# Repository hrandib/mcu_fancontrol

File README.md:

# Intent
The main intent of this solution is to provide the functionality similar to [PC Fancontrol](https://github.com/hrandib/pc_fancontrol) service but in hardware. There are a lot of equipment around which have fans and are quite noisy for no particular reason. Some of them even have fan controllers but algo/control curve is usually awful. This module can solve this issue.

# Brief features
 - The module provides 2 fan control PWM channels.
 - The first channel optionally is able to control 2-3pin fans by regulating DC voltage
 - The second channel is PWM only, this is PCB only limitation (4-pin fans)
 - Channels have independent configuration but can use shared sensors
 - Up to 8 sensors are supported, 4 sensors of type LM75 and 4 sensors of type DS18B20
 - Each controller channel can use up to 4 sensors of any type
 - Controller define:
   - poll period
   - algorithm: PI, 2-Point
   - sensors binding
   - MIN and MAX limits for PWM
   - EMA filtering, etc
 - The module configuration is performed via UART using PC side Python utility, it uses YAML format for the store/upload

# The Basic Workflow
1. Connect all the sensors to the board
2. Connect the board to PC and set active channels, e.g if you won't use the first channel it can be disabled. The command expects the list of active channel numbers separated by space

```shell
python .\fanutil.py -p tty... -e 0 1
```
3. Optionally mark channels as analog, it's needed only for proper display in configuration file, functionality is not affected. The command expects the list of analog channel numbers separated by space, an empty means all channels are PWM 

```shell
python .\fanutil.py -p tty... -a 0
```

4. Read current configuration, it'll contain all recognized sensors and controllers template.</br>The sample config is available [here](./datasheet/sample.yaml)

```shell
python .\fanutil.py -p tty... -r fanconfig.yaml
```

5. Edit the configuration file according to the fields description
6. Upload it to the board

```shell
python .\fanutil.py -p tty... -w fanconfig.yaml
```

# Possible alternatives

China market already provides various standalone fan control modules for less than 3 bucks.<br/>In many cases it's enough to solve the issue, but there are cases that can't be covered:
 - Multiple temperature measure points required
 - Multiple controller channels required with ability to share sensors
 - Other than 2-Point algo required, e.g to stabilize the temperature on the certain level

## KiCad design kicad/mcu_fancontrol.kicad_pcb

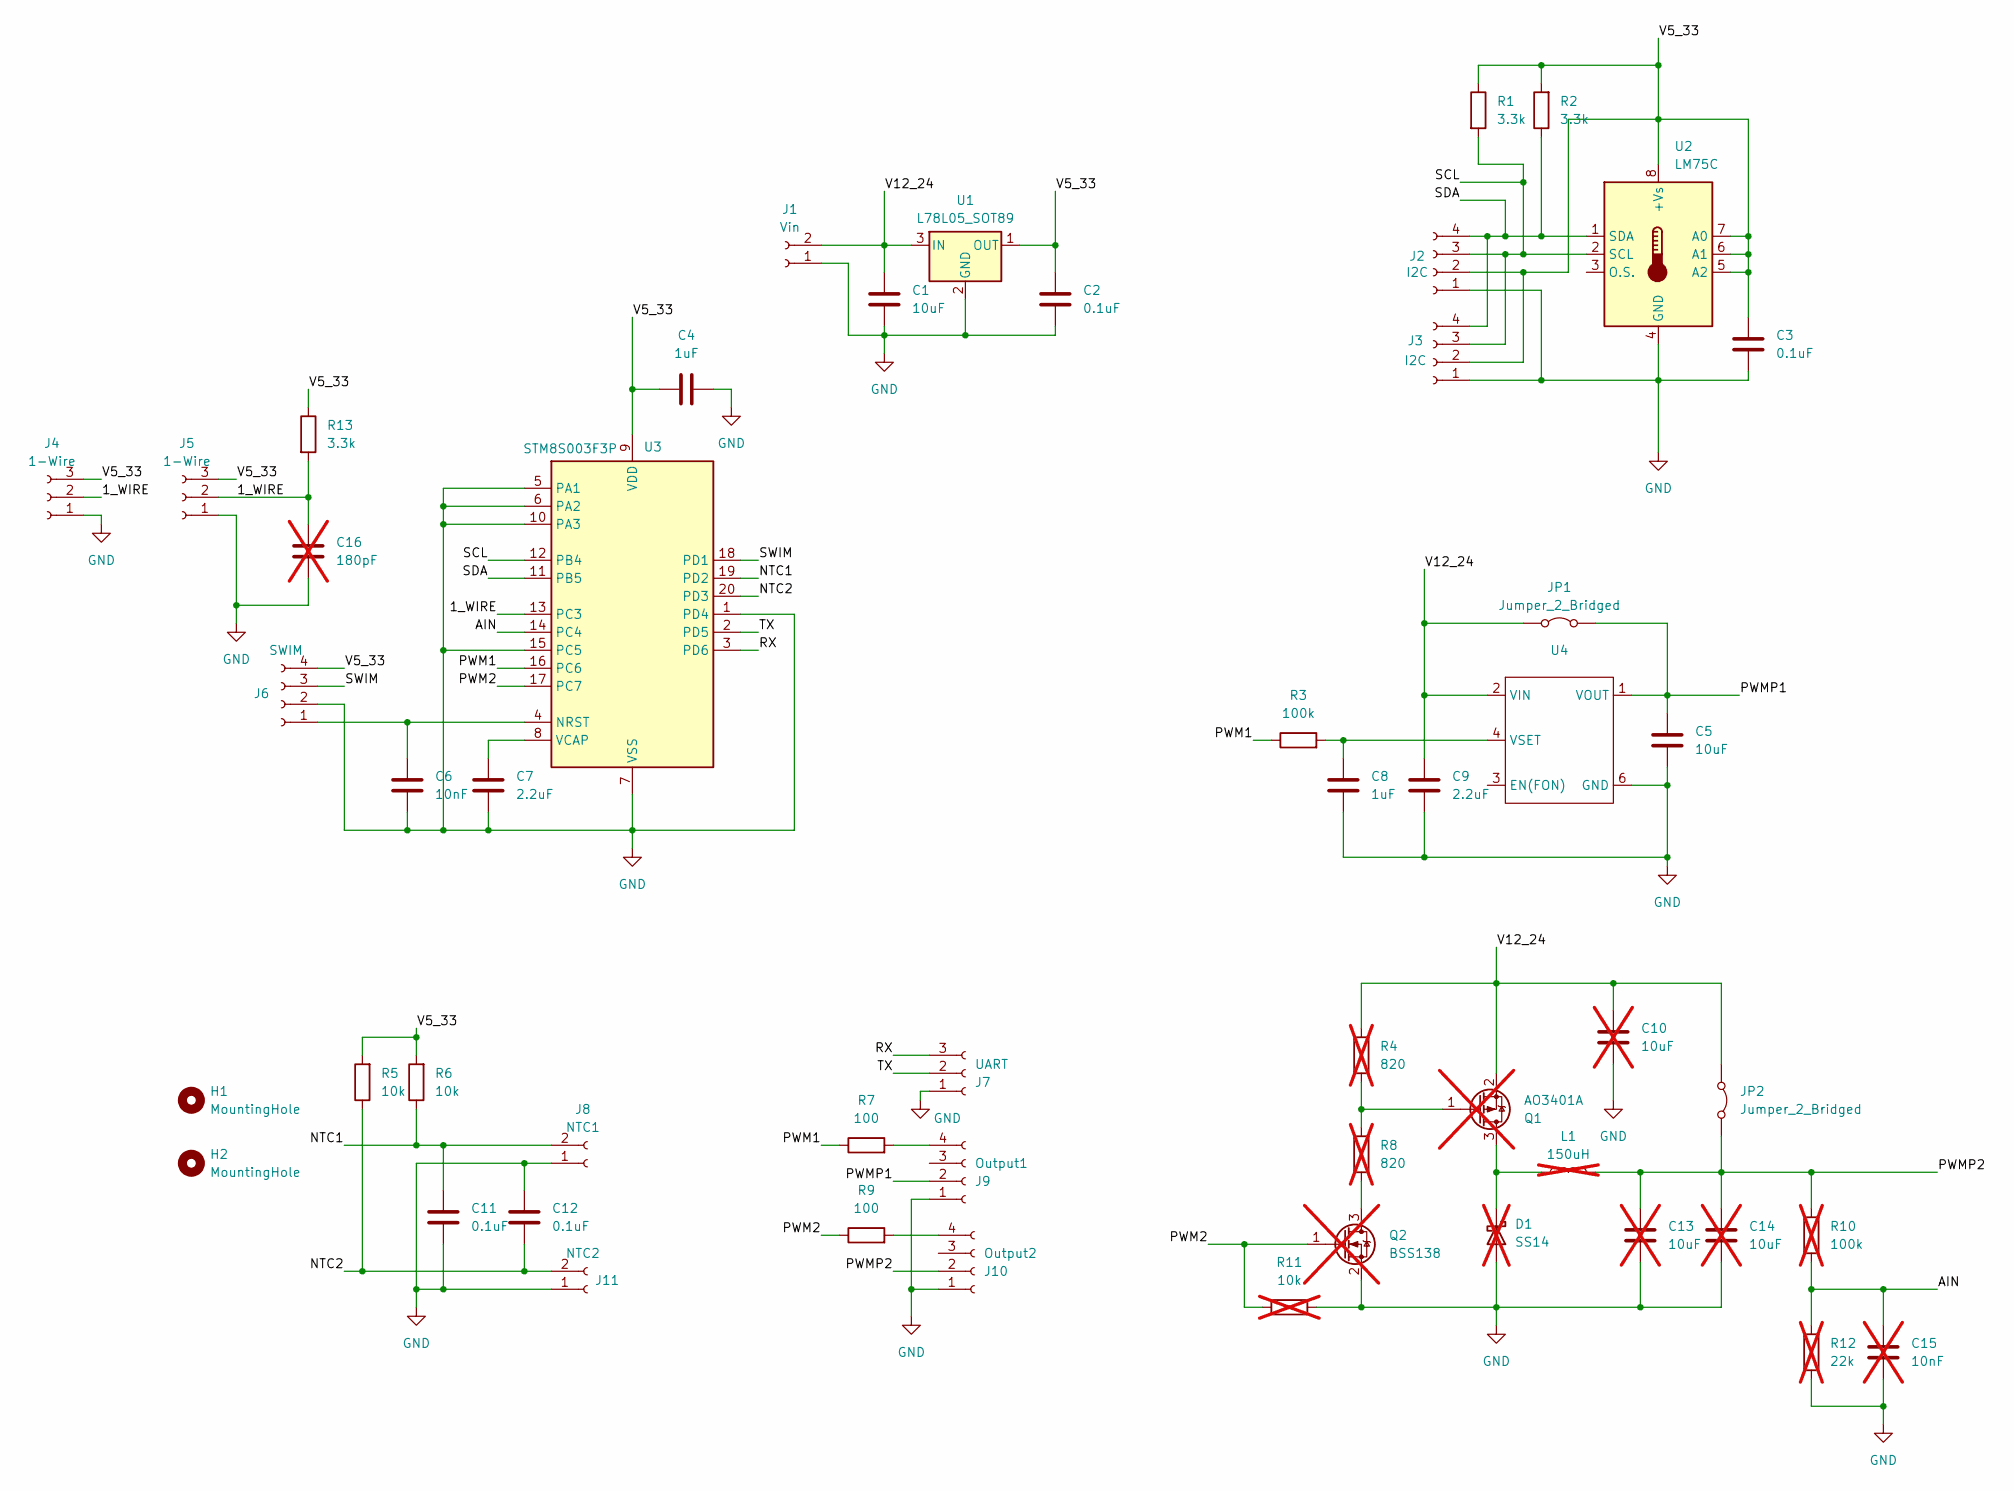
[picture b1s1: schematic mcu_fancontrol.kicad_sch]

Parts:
C1, C5: 10uF; C_1206_3216Metric
C2, C3, C11, C12: 0.1uF; C_0603_1608Metric
C4, C8: 1uF; C_0603_1608Metric
C6: 10nF; C_0603_1608Metric
C7, C9: 2.2uF; C_0603_1608Metric
C10, C13, C14: 10uF; C_1206_3216Metric; not fitted
C15: 10nF; C_0603_1608Metric; not fitted
C16: 180pF; C_0402_1005Metric_Pad0.74x0.62mm_HandSolder; not fitted
D1: SS14; D_SMA; not fitted
H1, H2: MountingHole; MountingHole_2.7mm_M2.5
J1: Vin; SolderWire-0.5sqmm_1x02_P4.8mm_D0.9mm_OD2.3mm
J2, J3: I2C; PinSocket_1x04_P2.54mm_Vertical
J4, J5: 1-Wire; PinSocket_1x03_P2.54mm_Vertical
J6: SWIM; PinSocket_1x04_P2.54mm_Vertical
J7: UART; PinSocket_1x03_P2.54mm_Vertical
J8: NTC1; PinHeader_1x02_P2.54mm_Vertical
J9: Output1; FanPinHeader_1x04_P2.54mm_Vertical
J10: Output2; FanPinHeader_1x04_P2.54mm_Vertical
J11: NTC2; PinHeader_1x02_P2.54mm_Vertical
JP1, JP2: Jumper_2_Bridged; SolderJumper-2_P1.3mm_Open_RoundedPad1.0x1.5mm
L1: 150uH; L_Radial_D7.0mm_P3.00mm; not fitted
Q1: AO3401A; SOT-23; not fitted
Q2: BSS138; SOT-23; not fitted
R1, R2, R13: 3.3k; R_0603_1608Metric
R3: 100k; R_0603_1608Metric
R4, R8: 820; R_1206_3216Metric; not fitted
R5, R6: 10k; R_0603_1608Metric
R7, R9: 100; R_0603_1608Metric
R10: 100k; R_0603_1608Metric; not fitted
R11: 10k; R_0603_1608Metric; not fitted
R12: 22k; R_0603_1608Metric; not fitted
U1: L78L05_SOT89; SOT-89-3
U2: LM75C; SOIC-8_3.9x4.9mm_P1.27mm
U3: STM8S003F3P; TSSOP-20_4.4x6.5mm_P0.65mm
U4: SOIC-8-1EP_3.9x4.9mm_P1.27mm_EP2.41x3.3mm_ThermalVias

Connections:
/1_WIRE: C16.1, J4.2, J5.2, R13.2, U3.13 (PC3)
/AIN: C15.1, R10.1, R12.2, U3.14 (PC4)
/NTC1: C11.1, J8.2, R6.1, U3.19 (PD2)
/NTC2: C12.2, J11.2, R5.1, U3.20 (PD3)
/PWM1: R3.1, R7.1, U3.16 (PC6)
/PWM2: Q2.1 (G), R9.1, R11.2, U3.17 (PC7)
/PWMP1: C5.1, J9.2, JP1.2 (B), U4.1 (VOUT)
/PWMP2: C13.2, C14.2, J10.2, JP2.2 (B), L1.2, R10.2
/RX: J7.3, U3.3 (PD6)
/SCL: J2.3, J3.3, R1.2, U2.2 (SCL), U3.12 (PB4)
/SDA: J2.4, J3.4, R2.1, U2.1 (SDA), U3.11 (PB5)
/SWIM: J6.3, U3.18 (PD1)
/TX: J7.2, U3.2 (PD5)
/V5_33: C2.1, C3.1, C4.1, J2.2, J3.2, J4.3, J5.3, J6.4, R1.1, R2.2, R5.2, R6.2, R13.1, U1.1 (OUT), U2.5 (A2), U2.6 (A1), U2.7 (A0), U2.8 (+Vs), U3.9 (VDD)
/V12_24: C1.1, C9.2, C10.2, J1.2, JP1.1 (A), JP2.1 (A), Q1.2 (S), R4.2, U1.3 (IN), U4.2 (VIN)
GND: C1.2, C2.2, C3.2, C4.2, C5.2, C6.2, C7.1, C8.1, C9.1, C10.1, C11.2, C12.1, C13.1, C14.1, C15.2, C16.2, D1.2 (A), J1.1, J2.1, J3.1, J4.1, J5.1, J6.2, J7.1, J8.1, J9.1, J10.1, J11.1, Q2.2 (S), R11.1, R12.1, U1.2 (GND), U2.4 (GND), U3.1 (PD4), U3.5 (PA1), U3.6 (PA2), U3.7 (VSS), U3.10 (PA3), U3.15 (PC5), U4.5 (NC), U4.6 (GND), U4.7 (NC), U4.8 (NC), U4.9 (PAD)
unnamed: D1.1 (K), L1.1, Q1.3 (D)
unnamed: C6.1, J6.1, U3.4 (NRST)
unnamed: J9.4, R7.2
unnamed: J10.4, R9.2
unnamed: Q1.1 (G), R4.1, R8.2
unnamed: Q2.3 (D), R8.1
unnamed: C7.2, U3.8 (VCAP)
unnamed: C8.2, R3.2, U4.4 (VSET)

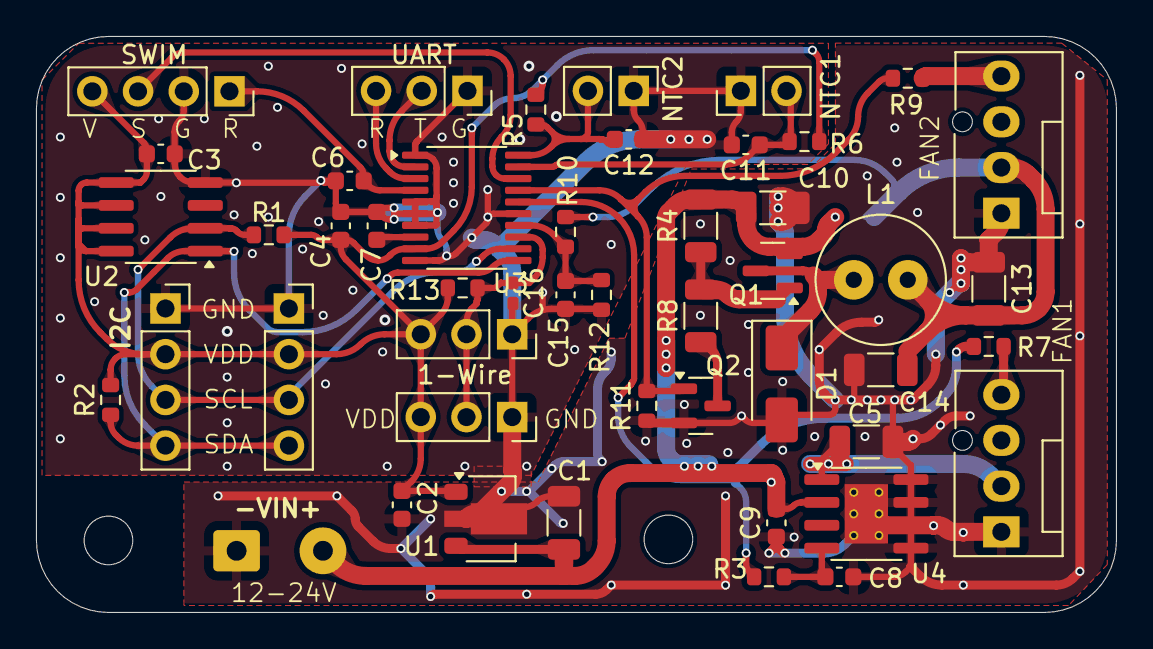
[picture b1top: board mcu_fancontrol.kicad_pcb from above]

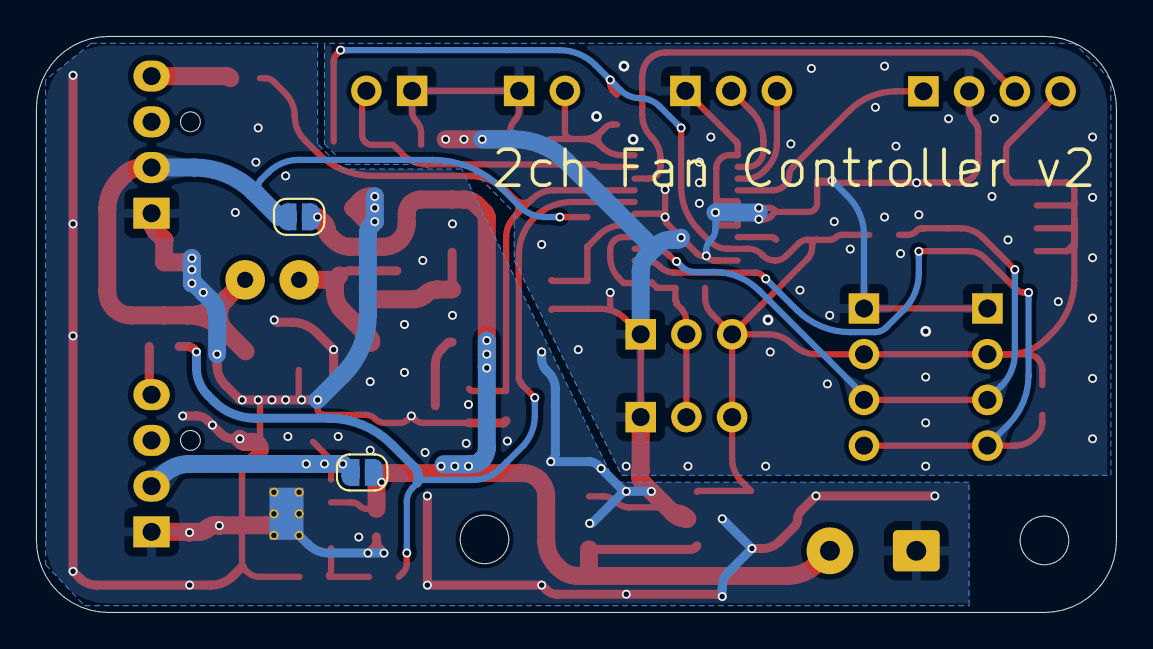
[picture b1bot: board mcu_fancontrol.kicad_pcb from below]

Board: 2 copper layers, 60.0 x 32.0 mm, 52 parts (2 on the bottom side), 24 nets.

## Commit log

2020-07-25 Initial schematic
2020-07-26 Add fan PWM specs
2020-07-26 Add pcb
2020-08-08 Add PCB connector labeling, minor design changes
2020-08-08 Add scmrtos, stm8_libs submodules
2020-08-08 Change scmrtos repo URL to own fork
2020-08-11 add qbs.user and build dir to gitignore
2020-08-11 Add base project definitions to qbs
2020-08-11 Add mcu flash script
2020-08-11 Add scmrtos and stm8lib to project build
2020-08-12 Compilation success
2020-08-15 Fully working project template
2020-08-15 LM75 driver in working state
2020-08-16 Add PWM fan control demo
2021-08-01 Fix .gitmodules syntax
2021-08-02 Fix flashing procedure
2021-08-09 Fix ScmRTOS warnings
2021-08-09 Add macros for RTOS task creation
2021-08-09 Add systicks to ms converters
2021-08-09 Cleanup main.cpp
2021-08-09 Draft implementation
2021-08-13 Add .clang-format file
2021-08-13 Reformat scmRTOS_CONFIG.h
2021-08-13 Fix MS2ST ST2MS macros
2021-08-13 Add __STDC_LIMIT_MACROS compilation option
2021-08-16 PWM Controller in the working state
2021-08-24 Move scm_utils from config to scm_aux dir
2022-02-07 Add BaseStream interface
2022-02-07 Add printing of section size
2022-02-08 Shell in the working state
2022-02-08 Remove Increment/Decrement handlers
2022-02-08 Add generic sensor interface
2022-02-08 Add DS18B20 datasheet
2022-02-08 Add missing license headers
2022-02-09 SensorHandler: add LM75 support
2022-02-09 DS18B20 reading demo
2022-02-09 Demo: print values from all sensors
2022-02-09 Tweak temperatures printing
2022-02-09 Add sample config file
2022-02-09 Remove sensor.h iface
2022-02-10 Initial controller skeleton
2022-02-10 Refactor. Drop UartStream dependency from SensorHandler
2022-02-10 Fix system timer frequency
2022-02-10 Fix sensors number handling
2022-02-10 Fix S2ST macro
2022-02-10 Rename stream arg in SHELL_FUNC
2022-02-10 Add ability to upload EEPROM content
2022-02-10 Add default EEPROM config
2022-02-11 Move PWM part to the separate module
2022-02-11 2 point algo in the working state
2022-02-11 PI algo in the working state
2022-02-11 Disable the shell due to flash size limit
2022-02-11 Fix formatting
2022-02-11 Remove shell impl
2022-02-13 Main instruction set in the working state
2022-02-14 Add support of the fan stop hysteresis
2022-02-14 Add Fan stop state GPIO output for CH2
2022-02-14 Sync stm8libs
2022-02-14 Rename Samples -> Utility
2022-02-14 Rename fancontrol.yaml -> sample.yaml
2022-02-14 Change to fixed packet size for Device info
2022-02-14 CLI utility initial implementation
2022-02-14 Add printing sensors and control structs
2022-02-15 Add crc check function
2022-02-15 Fix CRC value in the default ControlStruct
2022-02-15 Add CRC check while reading control structs
2022-02-15 Move sample configuration to Datasheet/
2022-02-15 Add ref.yaml, template config
2022-02-15 Update sample config
2022-02-15 Add config file generation
2022-02-15 Update sample remarks
2022-02-15 Add values normalization
2022-03-27 Update stm8_libs submodule
2022-05-28 Upload implemented
2022-06-12 Fix compilation on QtCreator 7
2022-06-12 Fix flashing script for QtCreator 7
2022-08-09 Make fanutil.py compatible with newer Python
2022-08-09 General refactor
2022-08-09 Add ready to use config for the Korad PS
2023-06-04 Add IWDG refresh, must be enable in option bytes
2023-06-04 Add FanStop pin notes to schematic and source
2023-06-04 Add stricter pollTimeCounter checking in controller.cpp
2023-06-04 Change device info channel number to mask
2023-06-04 Rename root directories to the lower case
2023-06-04 Fix BaseStream write length
2023-06-04 Lower DS18B20 resolution to 9-bit
2023-06-04 Explicitly exclude disabled channels from the main controller loop
2023-06-04 Change default channel number to 2
2023-06-04 Change DeviceInfo struct elements type to uint32
2023-06-04 Add channels number constant to the DeviceInfo struct
2023-06-04 Add selective printing of control structs
2023-06-05 Add support of the single channel configuration
2023-06-05 Add more informative sensor printing
2023-06-05 Add ability to set channel configuration
2023-06-05 Simplify set channels command
2023-06-05 Add command to mark analog channels
2023-06-05 Fix volatile for DeviceInfo
2023-06-05 Add comments for Kp and Ki params
2023-06-05 Add UART RX flushing
2023-06-05 Implement EMA filtering feature
2023-06-05 Fix EMA scale factor
2023-06-05 Improve robustness for the DS18B20 reading routine
2023-06-05 Add sensor ID bound check
2023-06-06 Define constant for the sensor reading delay
2023-06-06 Minor fix in the k_ema description
2023-06-06 Increase serial read timeout for the config write command
2023-06-06 Print sensor ID as raw hex in yaml
2023-06-06 Replace plain DS18 sensor IDs with IDs based on the sensor CRC
    This update resolves sensors configuration shifting and mix-up
    in the case of one of the sensors being damaged or missing.
    Though it introduces another issue, there is a probability of
    the sensors ID conflict, in this case, the conflicting sensor just
    will not be included in the configuration. This issue is less
    critical and doesn't have an influence on reliability unlike the
2023-06-06 Add README
2023-06-09 Remove Korad PS outdated config file
2023-11-27 Fix spurious unhandled GPIO interrupt
2024-06-03 Add kicad updated schematics
2024-06-08 Add new PCB design
2024-06-08 pcb: Add teadrops, round tracks
    Other minor fixes
2024-06-08 pcb: Fix silkscreen
2024-06-09 pcb: Fix ground plane
2024-06-09 pcb: Minor change in the ground plane
2024-08-14 pcb: Add iBOM
2024-08-14 src: Change 1-Wire pin to Pc3
2024-08-25 src: Drop CH_MAX_NUMBER re-define
2024-08-25 src: Set version number to 2.0
2024-08-25 src: Set F_CPU clock 8MHz
2024-08-25 src: Update RTOS tick rate to 244Hz
2024-08-25 src: Enable hardware watchdog in firmware
    Force watchdog enablement regardless option bytes state
2024-08-25 pcb: Add optional RC filter for 1-Wire
2024-08-25 src: Increase the conversion time
2024-08-25 src: Improve sensor fault detection
2024-08-25 src: Add 3rd relay fan control output
2024-08-25 util: Relax Python libs version reqs
2024-08-25 src: Replace CRLF to LF in main.cpp
2024-09-09 util: Fix sensor indexing in yaml
    Controllers were stored to yaml incorrectly,
    Sensor indexes mapping is fixed
